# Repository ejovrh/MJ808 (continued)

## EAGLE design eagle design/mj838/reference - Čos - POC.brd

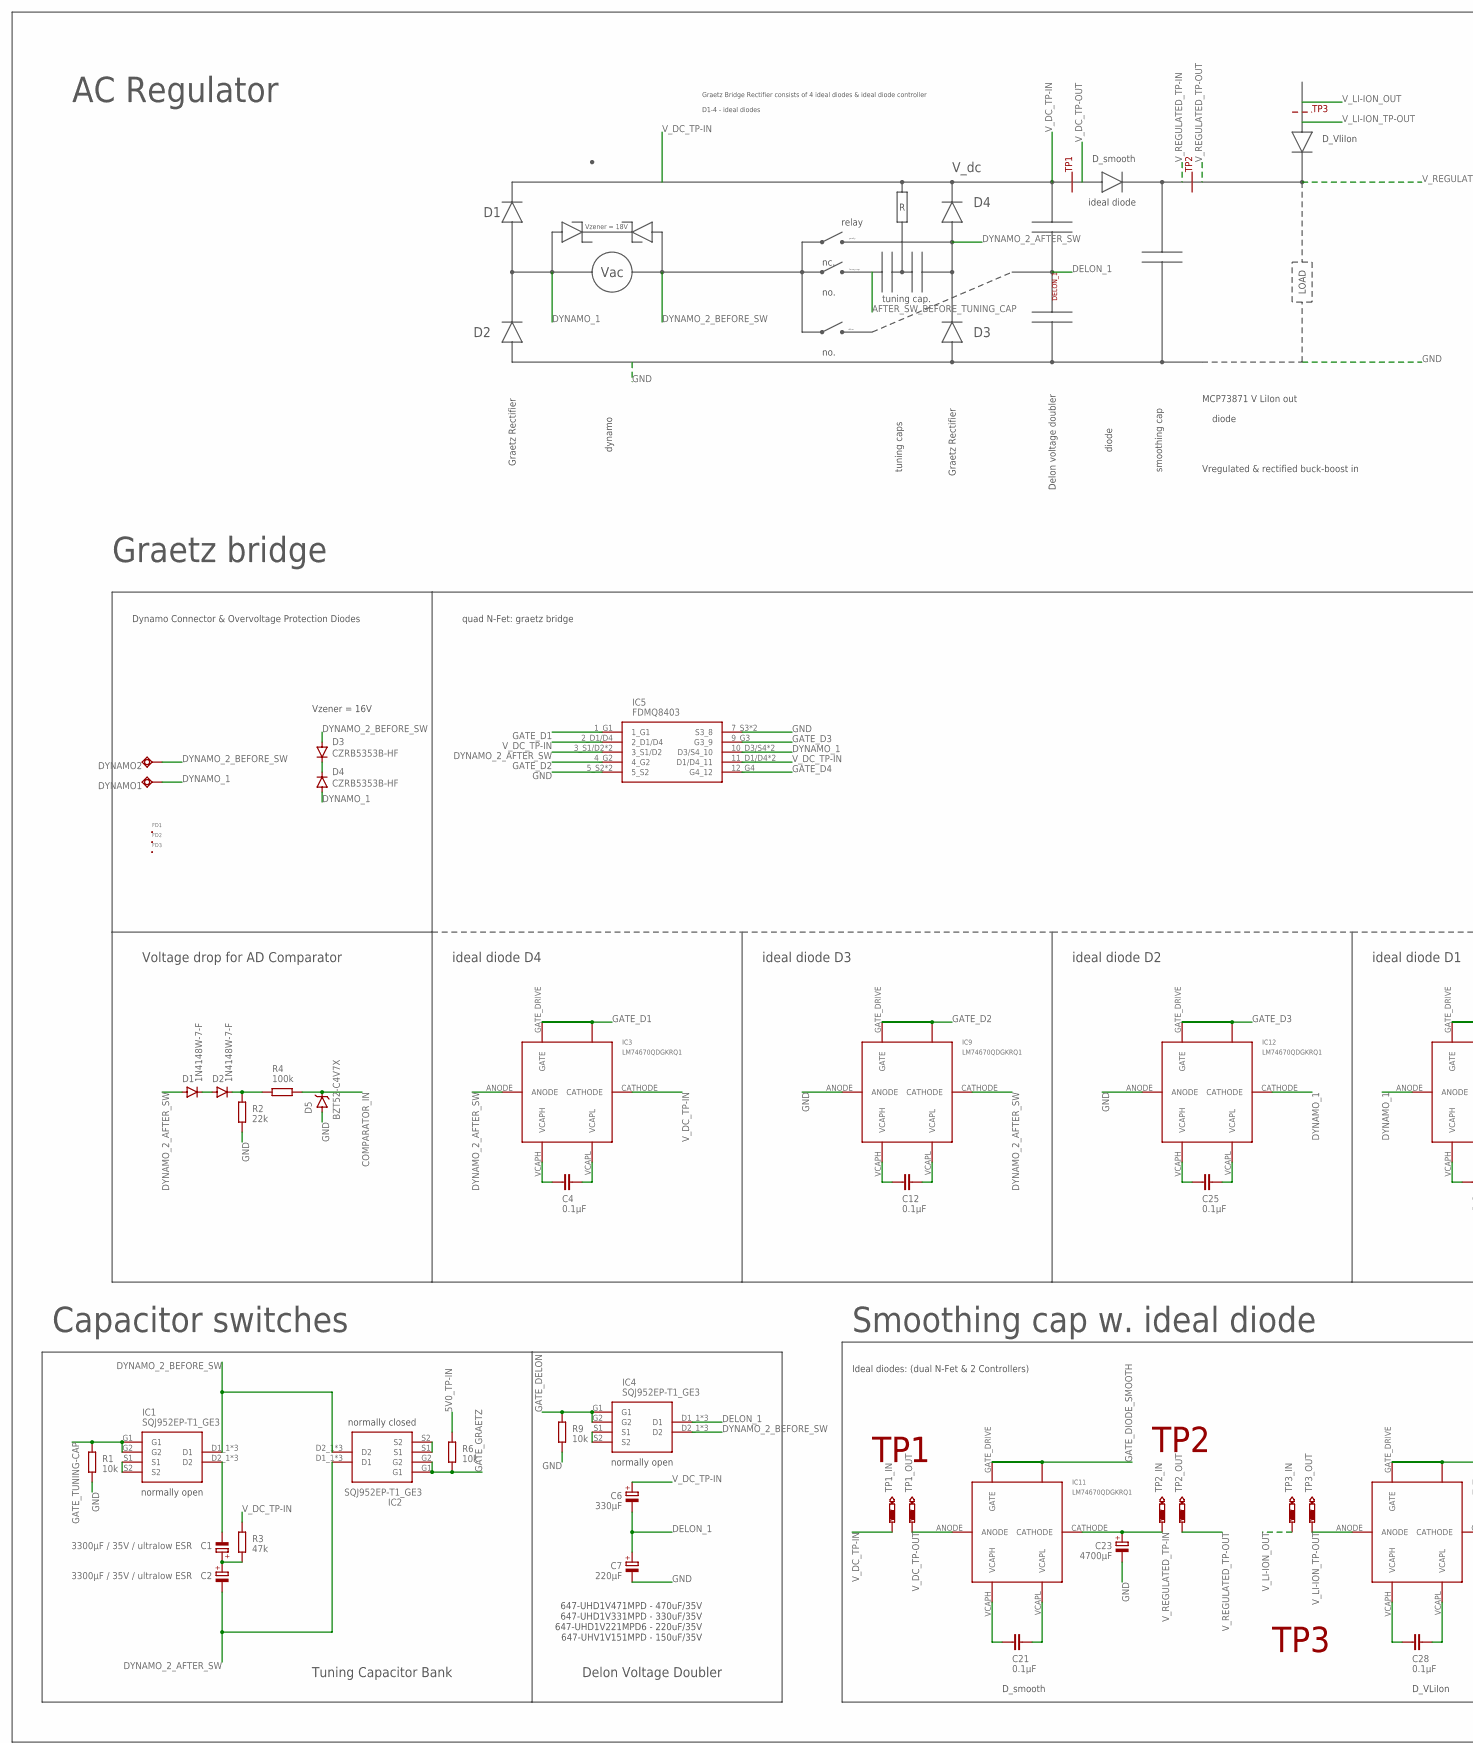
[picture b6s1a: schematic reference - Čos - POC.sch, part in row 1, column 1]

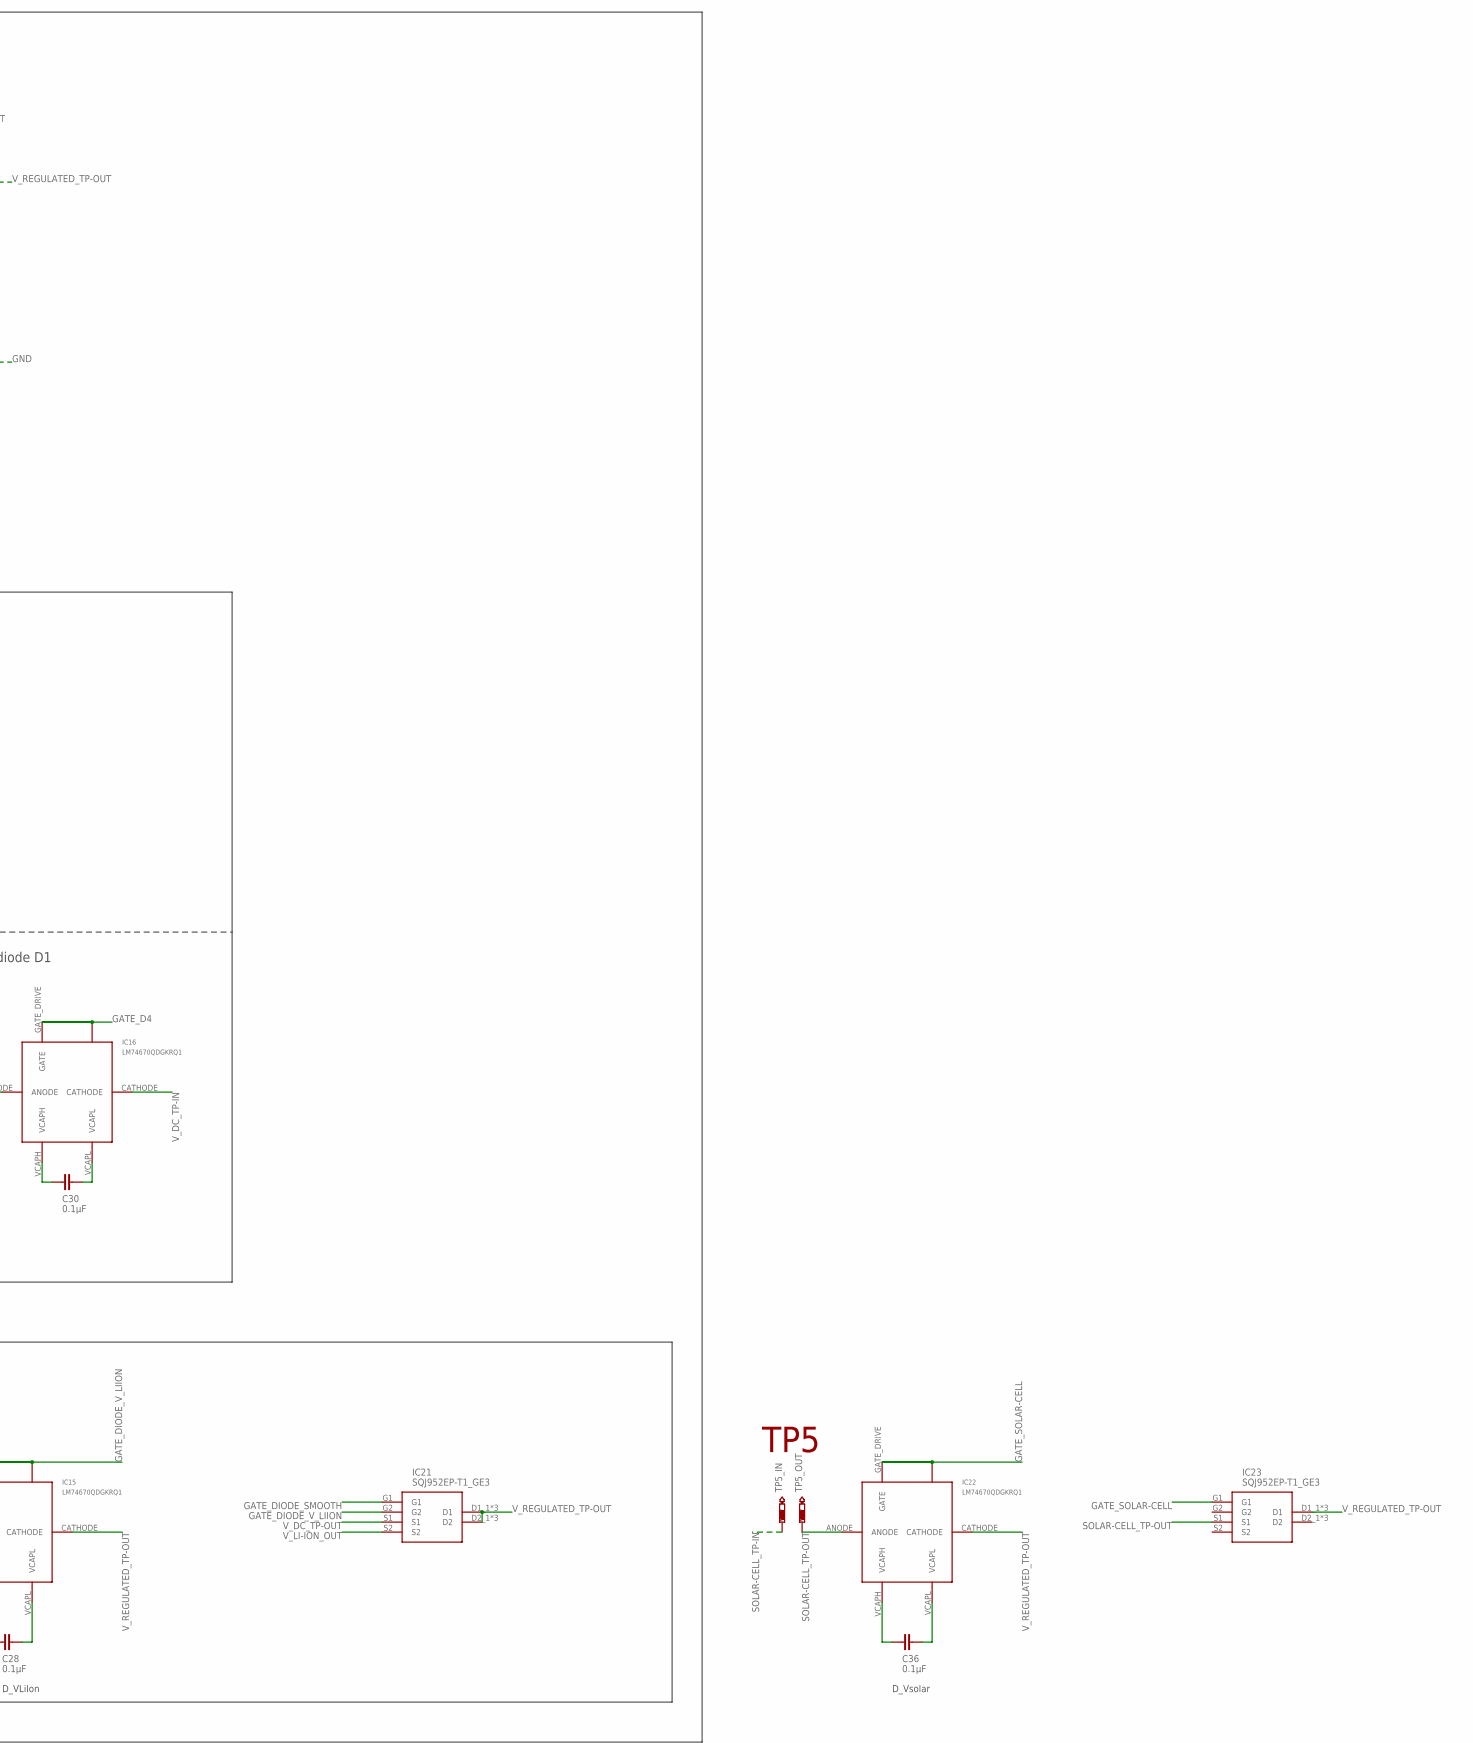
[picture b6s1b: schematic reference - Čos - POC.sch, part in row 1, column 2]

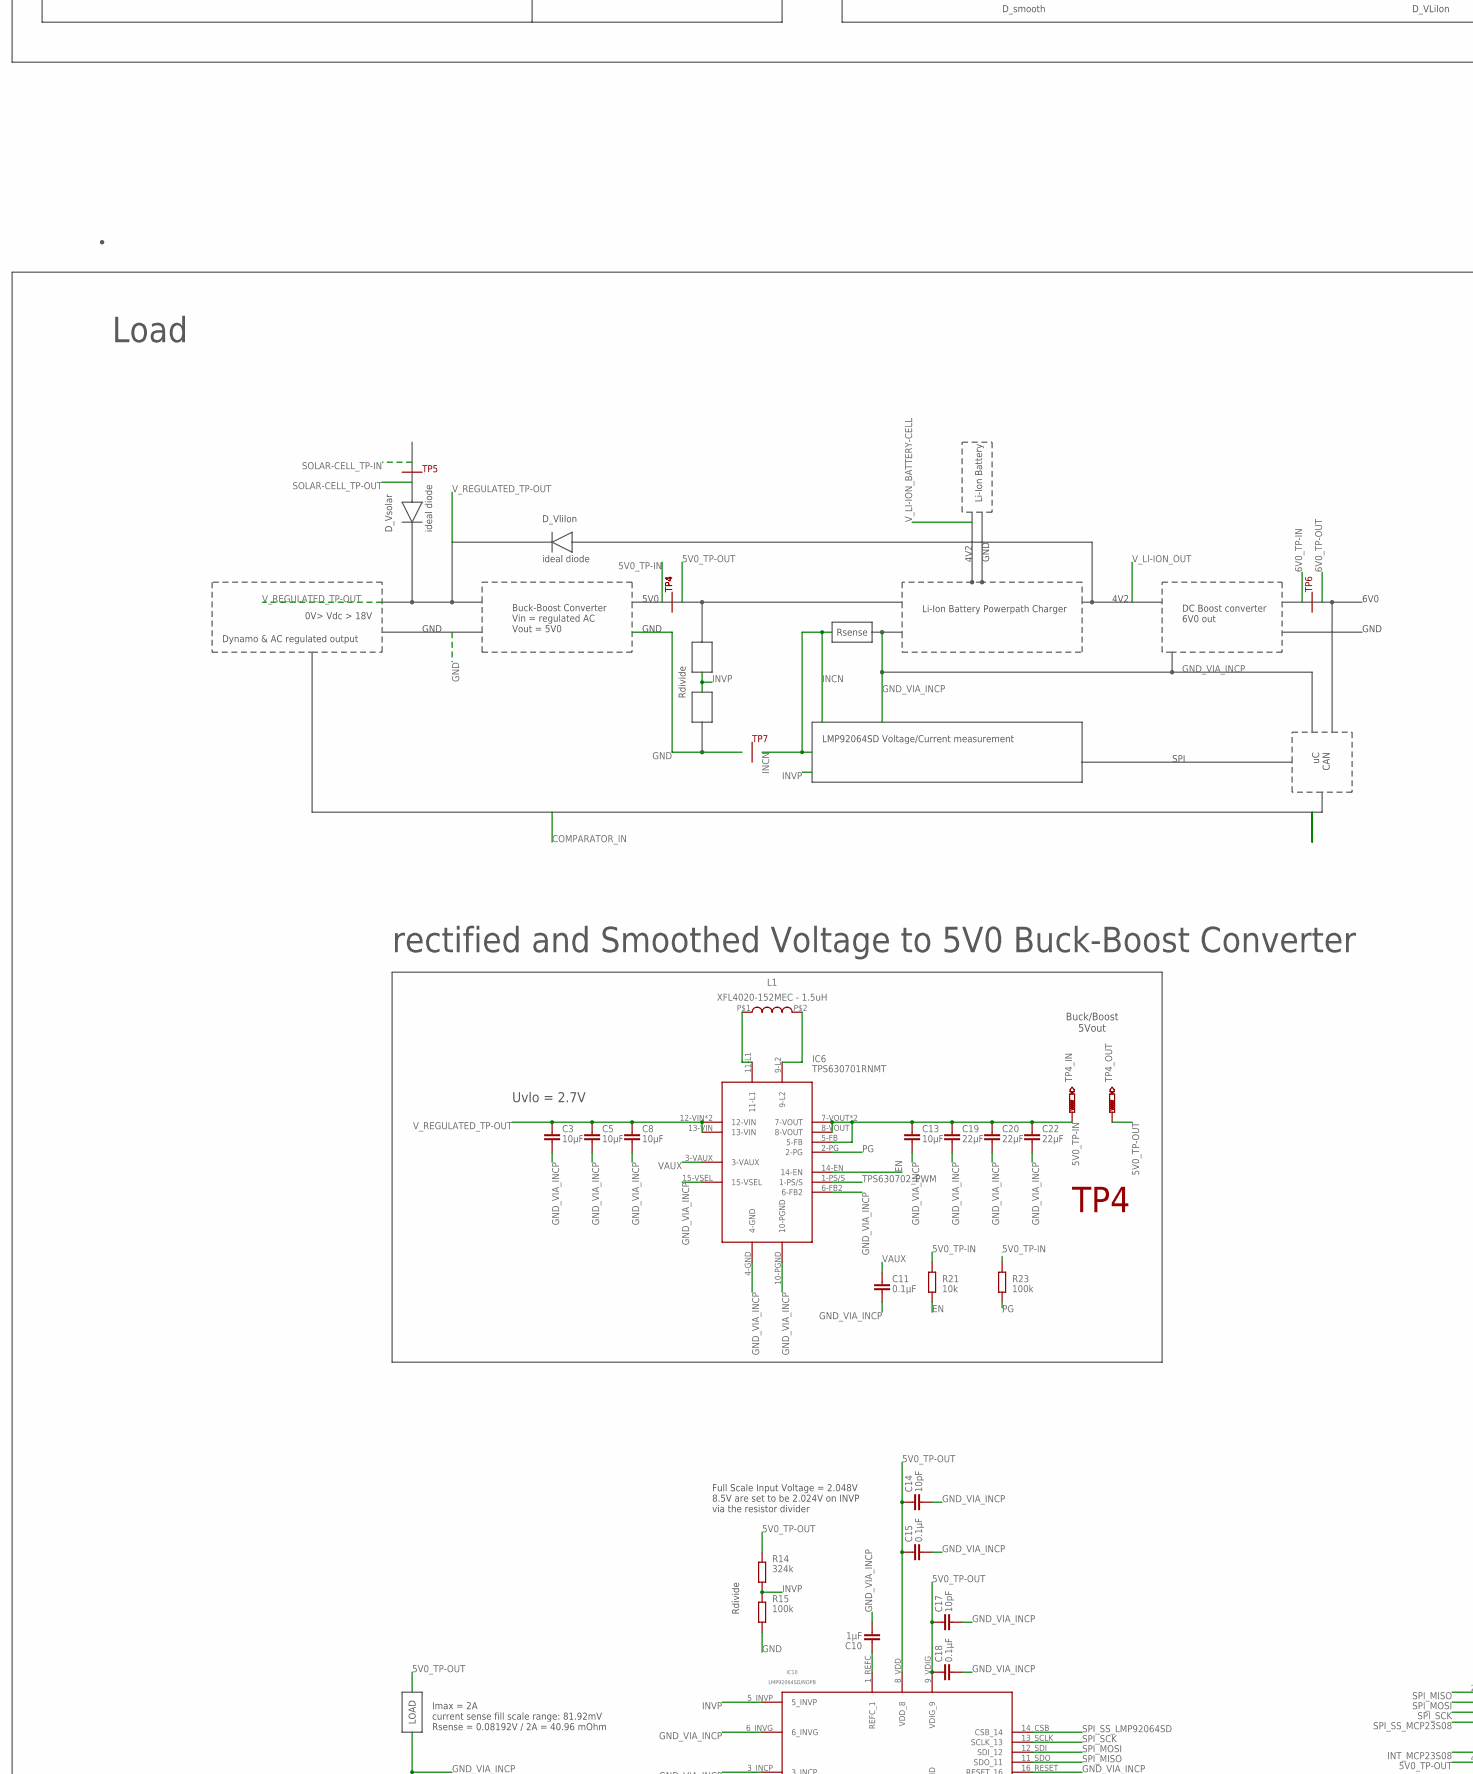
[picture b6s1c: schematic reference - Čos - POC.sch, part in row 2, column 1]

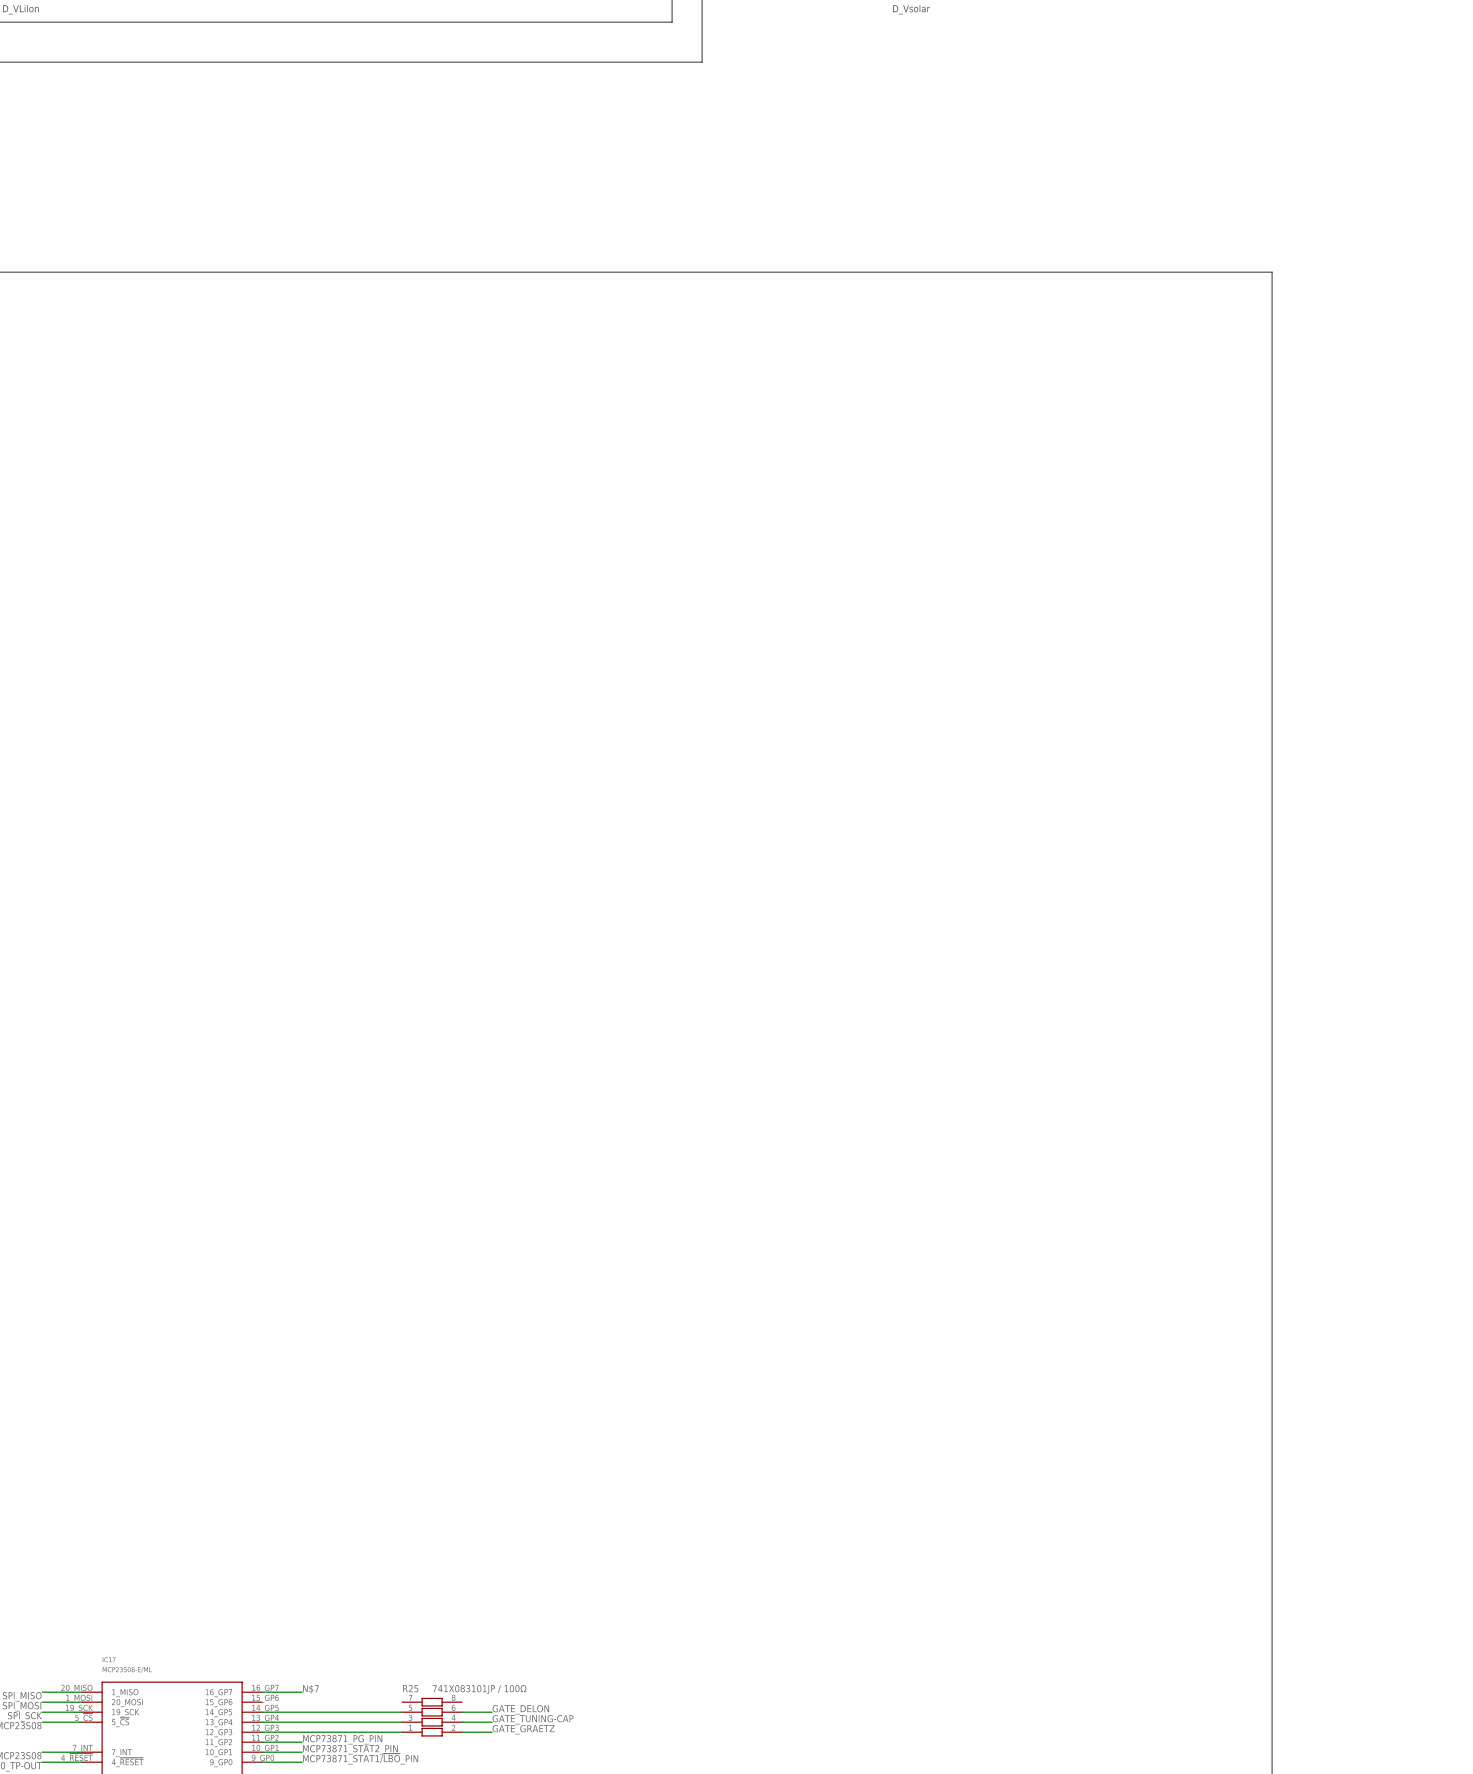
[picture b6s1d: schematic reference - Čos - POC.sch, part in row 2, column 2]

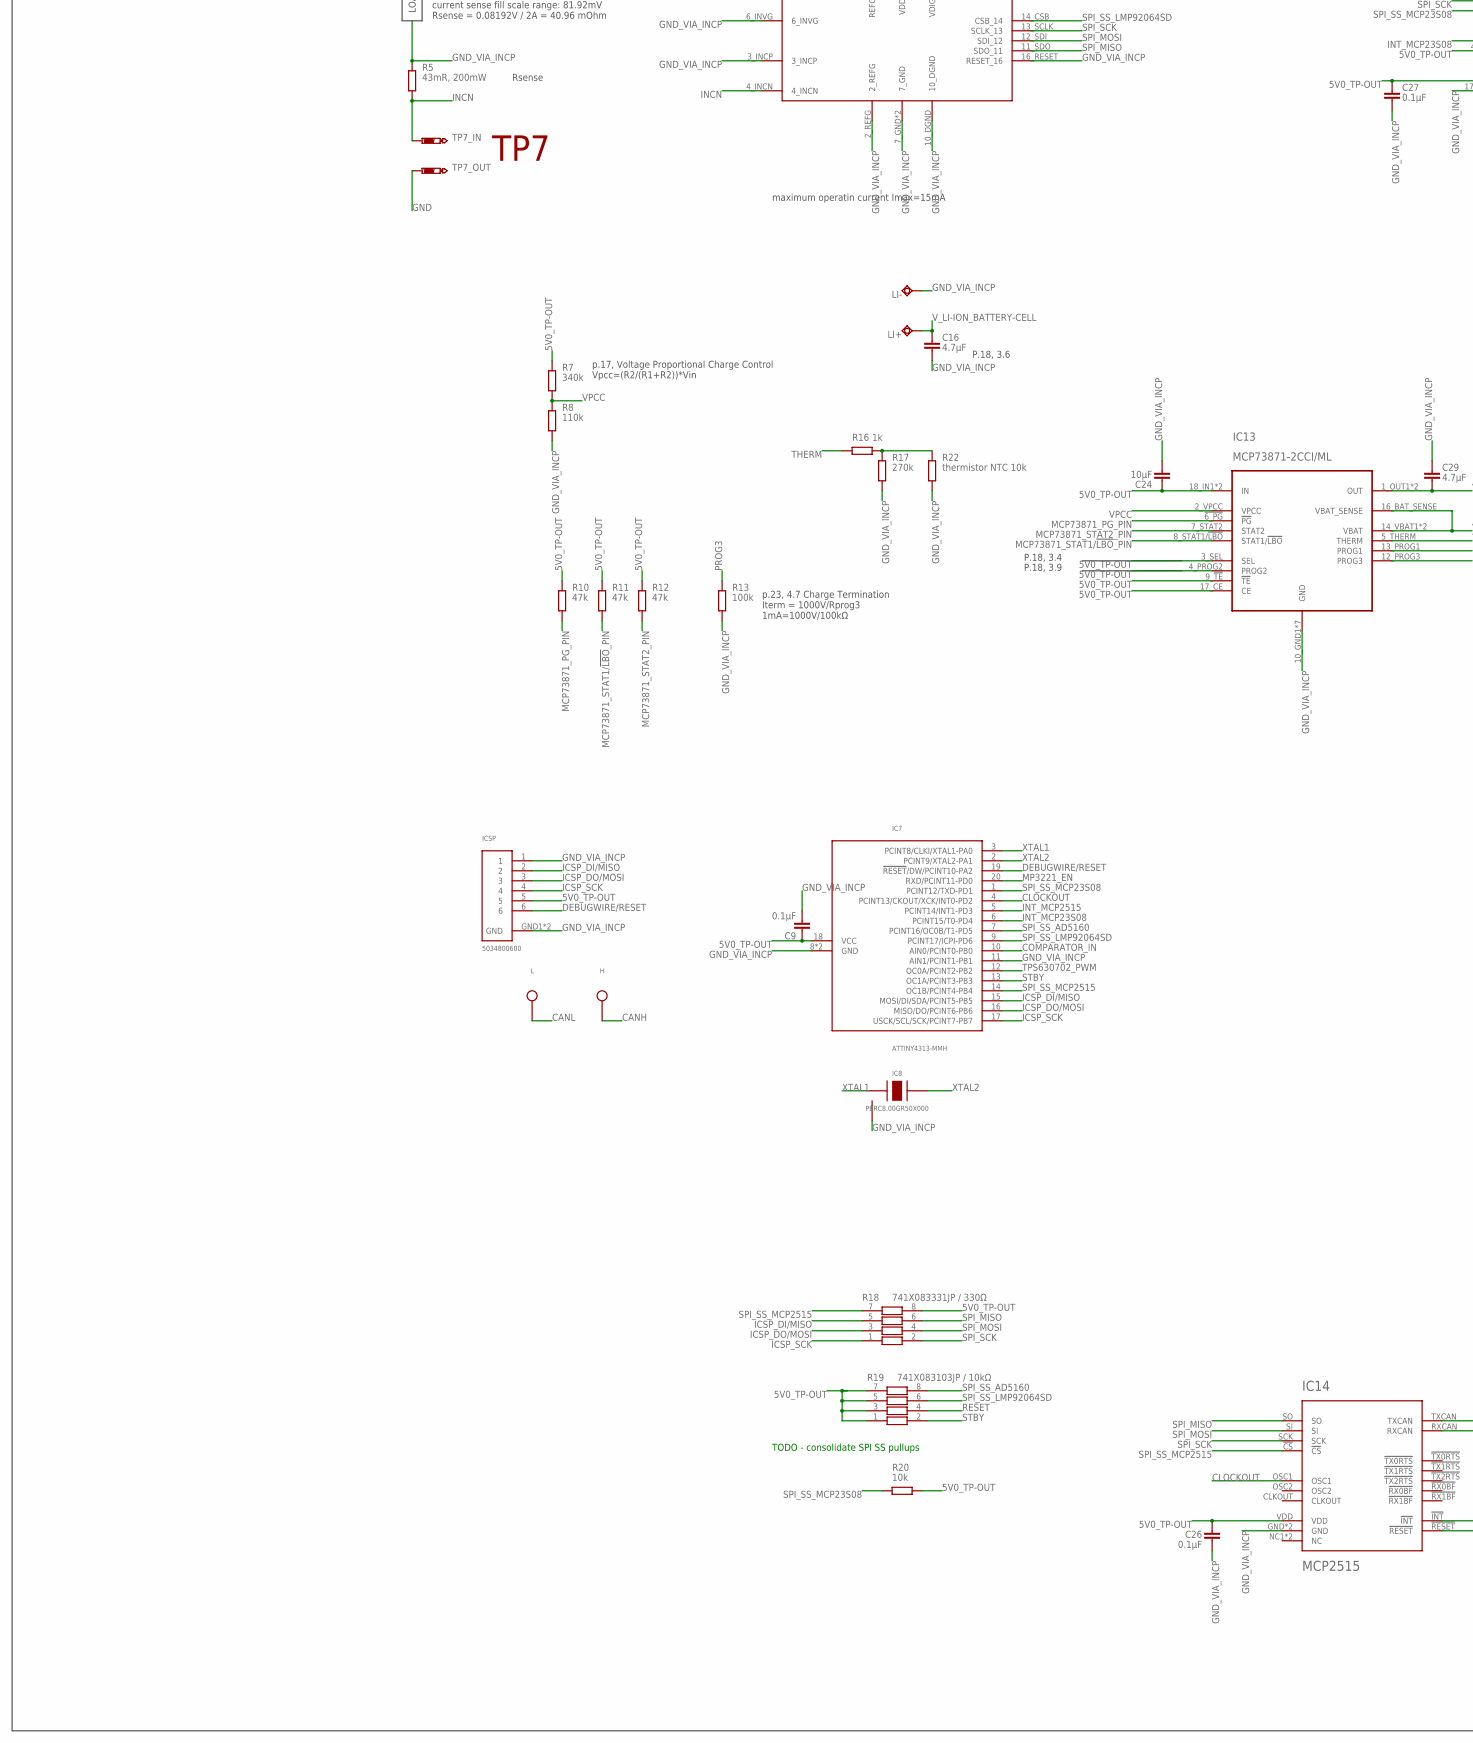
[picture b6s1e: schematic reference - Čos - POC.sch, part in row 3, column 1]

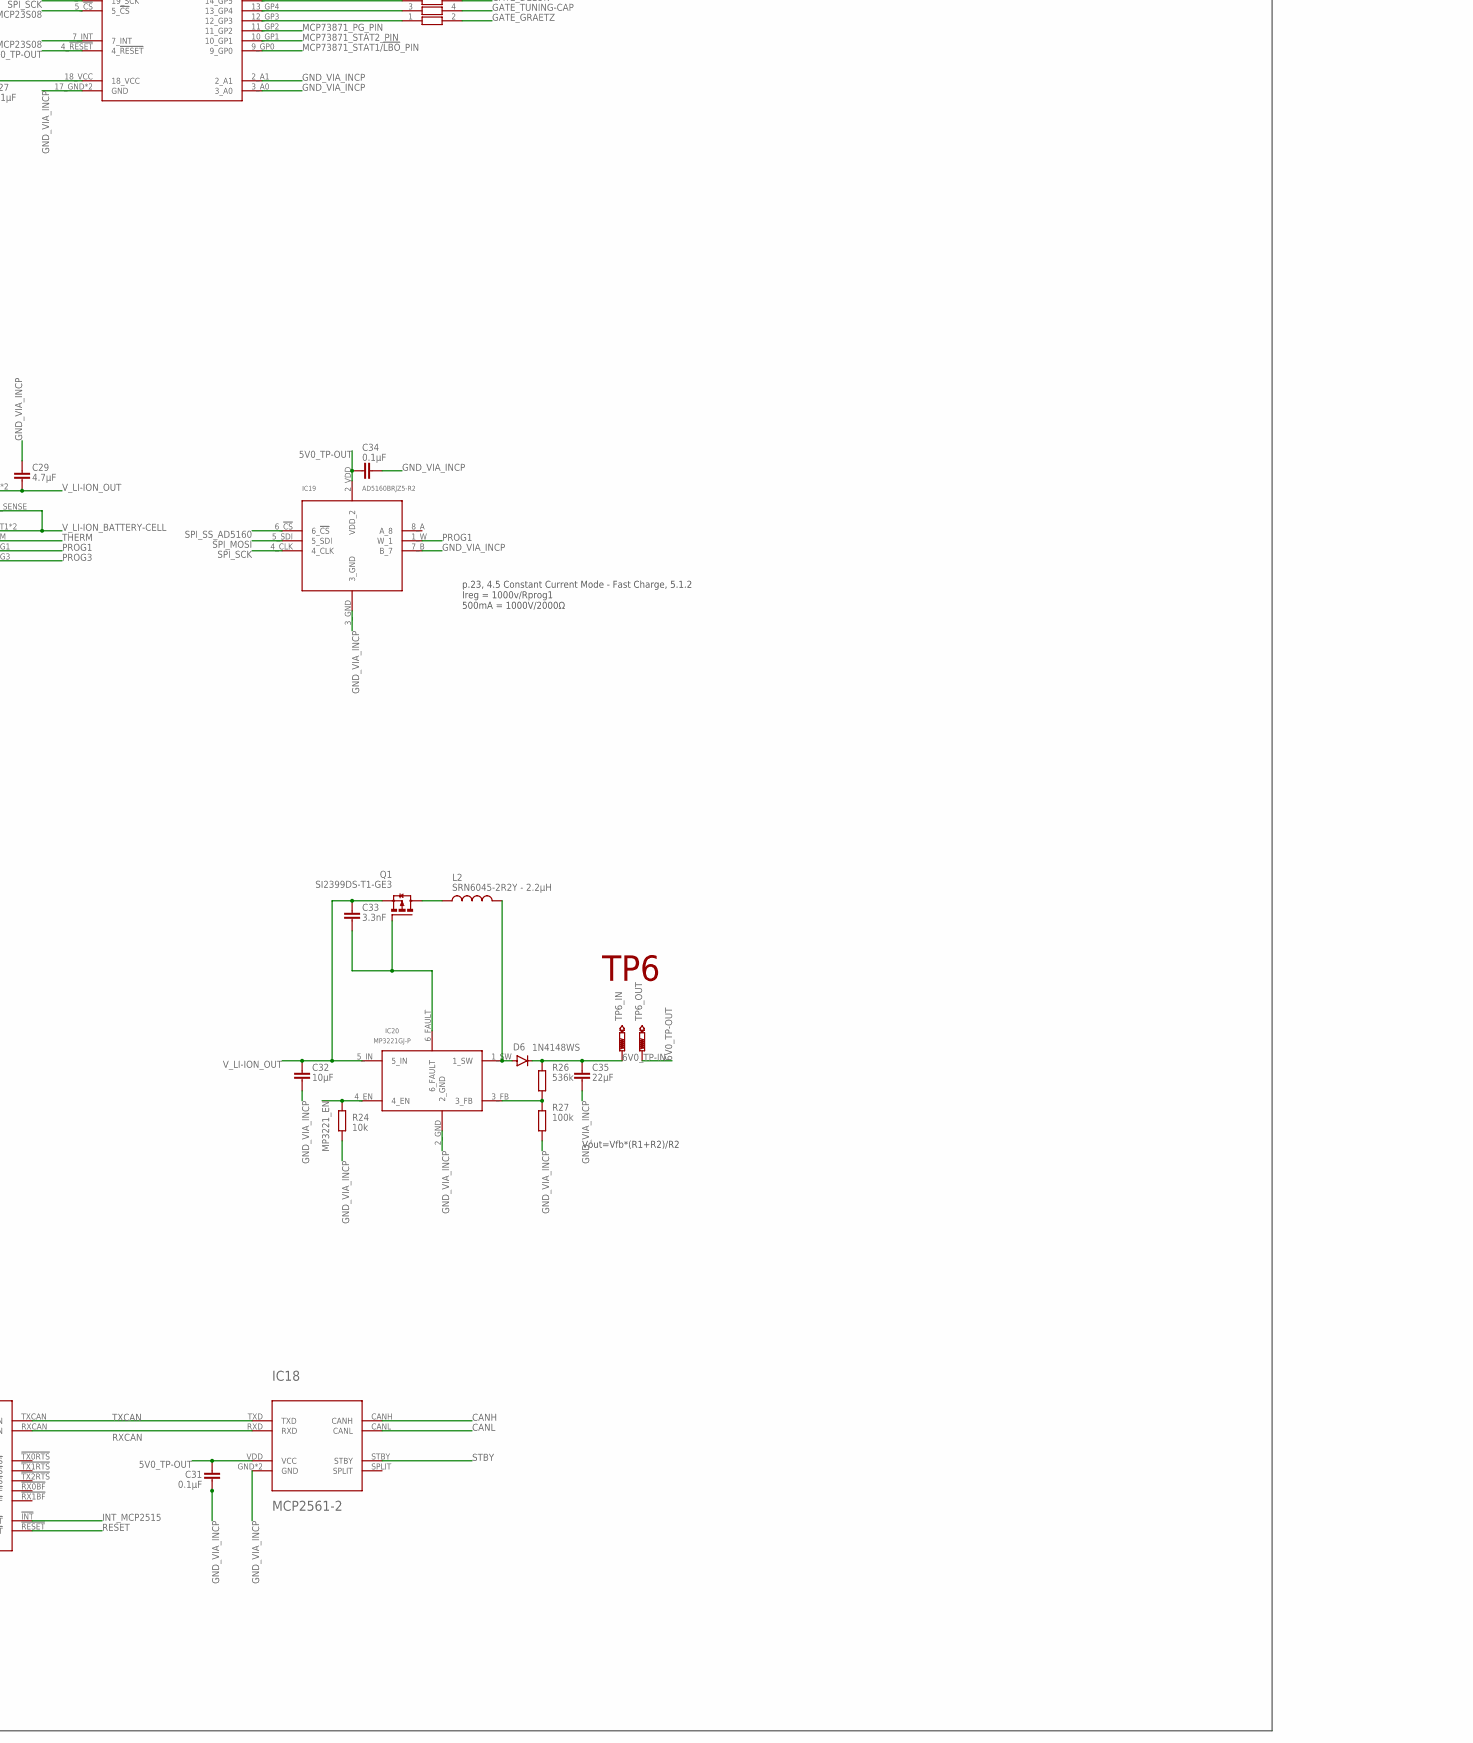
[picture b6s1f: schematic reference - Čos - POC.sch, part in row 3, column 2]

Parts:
C1, C2: 3300μF / 35V / ultralow ESR; E1,8-4
C3, C5: 10μF; C0805
C4, C9, C11, C12, C15, C18, C21, C25, C26, C27, C28, C30, C31, C34, C36: 0.1μF; C0402
C6: 330μF; E1,8-4
C7: 220μF; E1,8-4
C8, C13: 10μF; C0603
C10: 1μF; C0402
C14, C17: 10pF; C0402
C16, C29: 4.7μF; C0402
C19, C20, C22, C35: 22μF; C0805
C23: 4700μF; E1,8-4
C24, C32: 10μF; C0402
C33: 3.3nF; C0402
D1, D2: 1N4148W-7-F; SOD-123_MINI-SMA
D3, D4: CZRB5353B-HF; DO214AA
D5: BZT52-C4V7X; SOD-123
D6: 1N4148WS; SOD-323
DYNAMO1, DYNAMO2: Li-Ion Cell +; P1-13
FD1, FD2, FD3: FID_40MIL; FID_040
H: CAN High; SMT-1.2MM
IC1, IC2, IC4, IC21, IC23: SQJ952EP-T1_GE3; SO-8L
IC3, IC9, IC11, IC12, IC15, IC16, IC22: LM74670QDGKRQ1; VSSOP-8
IC5: FDMQ8403; MLP-12
IC6: TPS630701RNMT; VQFN
IC7: ATTINY4313-MMH; VQFN-20
IC8: PBRC8.00GR50X000; SMT
IC10: LMP92064SD/NOPB; WSON-16
IC13: MCP73871-2CCI/ML; QFN50P400X400X100-21N
IC14: MCP2515; QFN20
IC17: MCP23S08-E/ML; QFN20
IC18: MCP2561-2; DFN10
IC19: AD5160BRJZ5-R2; SOT-23-8
IC20: MP3221GJ-P; TSOT23-6
ICSP: 5034800600; SMT
L: CAN Low; SMT-1.2MM
L1: XFL4020-152MEC - 1.5uH; SMD
L2: SRN6045-2R2Y - 2.2μH; DJNR6045-100-S
LI+: Li-Ion Cell +; P1-13
LI-: Li-Ion Cell +; P1-13
Q1: SI2399DS-T1-GE3; SOT23
R1, R6, R9, R20, R21, R24: 10k; R0402
R2: 22k; R0402
R3, R10, R11, R12: 47k; R0402
R4, R13, R15, R23, R27: 100k; R0402
R5: 43mR, 200mW; R2512
R7: 340k; R0402
R8: 110k; R0402
R14: 324k; R0402
R16: 1k; R0402
R17: 270k; R0402
R18: 741X083331JP / 330Ω; 0402
R19: 741X083103JP / 10kΩ; 0402
R22: thermistor NTC 10k; V526-0
R25: 741X083101JP / 100Ω; 0402
R26: 536k; R0402
TP1_IN, TP1_OUT, TP2_IN, TP2_OUT, TP3_IN, TP3_OUT, TP4_IN, TP4_OUT, TP5_IN, TP5_OUT, TP6_IN, TP6_OUT, TP7_IN, TP7_OUT: PTR1TP10SQ; TP10SQ

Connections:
5V0_TP-IN: C13.1, C19.1, C20.1, C22.1, IC6.5-FB, IC6.7-VOUT, IC6.8-VOUT, IC6.VOUT (7-VOUT), R6.2, R21.2, R23.2, TP4_IN.TP
5V0_TP-OUT: C9.1, C14.1, C15.1, C17.1, C18.1, C24.1, C26.1, C27.1, C31.1, C34.1, IC7.18 (VCC), IC10.8_VDD (VDD_8), IC10.9_VDIG (VDIG_9), IC13.3_SEL (SEL), IC13.4_PROG2 (PROG2), IC13.9_!TE! (!TE!), IC13.17_CE (CE), IC13.18_IN1 (IN), IC13.19_IN2 (IN), IC14.VDD, IC17.4_!RESET!, IC17.18_VCC, IC18.VDD (VCC), IC19.2_VDD (VDD_2), ICSP.5, R7.2, R10.2, R11.2, R12.2, R14.2, R18.8, R19.1, R19.3, R19.5, R19.7, R20.2, TP4_OUT.TP
6V0_TP-IN: C35.1, D6.C, R26.2, TP6_IN.TP
6V0_TP-OUT: TP6_OUT.TP
AFTER_SW_BEFORE_TUNING_CAP: C1.-, IC1.D2_1 (D2), IC1.D2_2 (D2), IC1.D2_3 (D2)
CANH: H.P$1, IC18.CANH
CANL: IC18.CANL, L.P$1
CLOCKOUT: IC7.4 (PCINT13/CKOUT/XCK/INT0-PD2), IC14.OSC1
COMPARATOR_IN: D5.C, IC7.10 (AIN0/PCINT0-PB0), R4.2
D1_VCAPH: C4.2, IC3.VCAPH
D1_VCAPL: C4.1, IC3.VCAPL
D2_VCAPH: C12.2, IC9.VCAPH
D2_VCAPL: C12.1, IC9.VCAPL
D3_VCAPH: C25.2, IC12.VCAPH
D3_VCAPL: C25.1, IC12.VCAPL
D4_VCAPH: C30.2, IC16.VCAPH
D4_VCAPL: C30.1, IC16.VCAPL
DEBUGWIRE/RESET: IC7.19 (!RESET!/DW/PCINT10-PA2), ICSP.6
DELON_1: C6.-, C7.+, IC4.D1_1 (D1), IC4.D1_2 (D1), IC4.D1_3 (D1)
DYNAMO_1: D4.A, DYNAMO1.TP, IC5.10_D3/S4 (D3/S4_10), IC5.D3/S4 (D3/S4_10), IC12.CATHODE, IC16.ANODE
DYNAMO_2_AFTER_SW: C2.-, D1.A, IC2.D1_1 (D1), IC2.D1_2 (D1), IC2.D1_3 (D1), IC3.ANODE, IC5.3_S1/D2, IC5.S1/D2 (3_S1/D2), IC9.CATHODE
DYNAMO_2_BEFORE_SW: D3.A, DYNAMO2.TP, IC1.D1_1 (D1), IC1.D1_2 (D1), IC1.D1_3 (D1), IC2.D2_1 (D2), IC2.D2_2 (D2), IC2.D2_3 (D2), IC4.D2_1 (D2), IC4.D2_2 (D2), IC4.D2_3 (D2)
D_SMOOTH_VCAP: C21.1, IC11.VCAPL
D_SMOOTH_VCAPH: C21.2, IC11.VCAPH
D_VLIION_VCAPH: C28.2, IC15.VCAPH
D_VLIION_VCAPH1: C36.2, IC22.VCAPH
D_VLIION_VCAPL: C28.1, IC15.VCAPL
D_VLIION_VCAPL1: C36.1, IC22.VCAPL
EN: IC6.14-EN, R21.1
FB: IC20.3_FB, R26.1, R27.2
GATE_D1: IC3.GATE_DRIVE (GATE), IC3.GATE_PULLD, IC5.1_G1
GATE_D2: IC5.4_G2, IC9.GATE_DRIVE (GATE), IC9.GATE_PULLD
GATE_D3: IC5.9_G3 (G3_9), IC12.GATE_DRIVE (GATE), IC12.GATE_PULLD
GATE_D4: IC5.12_G4 (G4_12), IC16.GATE_DRIVE (GATE), IC16.GATE_PULLD
GATE_DELON: IC4.G1, IC4.G2, R9.2, R25.6
GATE_DIODE_SMOOTH: IC11.GATE_DRIVE (GATE), IC11.GATE_PULLD, IC21.G1
GATE_DIODE_V_LIION: IC15.GATE_DRIVE (GATE), IC15.GATE_PULLD, IC21.G2
GATE_GRAETZ: IC2.G1, IC2.G2, R6.1, R25.2
GATE_SOLAR-CELL: IC22.GATE_DRIVE (GATE), IC22.GATE_PULLD, IC23.G1
GATE_TUNING-CAP: IC1.G1, IC1.G2, R1.2, R25.4
GND: C7.-, C23.-, D5.A, IC5.5_S2, IC5.6_S2 (5_S2), IC5.7_S3 (S3_8), IC5.8_S3 (S3_8), IC9.ANODE, IC12.ANODE, R1.1, R2.1, R9.1, R15.1, TP7_OUT.TP
GND_VIA_INCP: C3.2, C5.2, C8.2, C9.2, C10.2, C11.2, C13.2, C14.2, C15.2, C16.2, C17.2, C18.2, C19.2, C20.2, C22.2, C24.2, C26.2, C27.2, C29.1, C31.2, C32.2, C34.2, C35.2, IC6.4-GND, IC6.6-FB2, IC6.10-PGND, IC6.15-VSEL, IC7.8 (GND), IC7.11 (AIN1/PCINT1-PB1), IC7.GND, IC8.GND, IC10.2_REFG, IC10.3_INCP, IC10.6_INVG, IC10.7_GND, IC10.10_DGND, IC10.16_RESET (RESET_16), IC10.GND1 (7_GND), IC13.10_GND1 (GND), IC13.11_GND2 (GND), IC13.GND2 (GND), IC13.GND3 (GND), IC13.GND4 (GND), IC13.GND5 (GND), IC13.GND6 (GND), IC14.GND, IC14.GND6 (GND), IC17.2_A1, IC17.3_A0, IC17.17_GND (GND), IC17.GND, IC18.GND, IC18.VSS (GND), IC19.3_GND, IC19.7_B (B_7), IC20.2_GND, ICSP.1, ICSP.GND1 (GND), ICSP.GND2 (GND), LI-.TP, R5.2, R8.1, R13.1, R17.1, R22.1, R24.2, R27.1
ICSP_DI/MISO: IC7.15 (MOSI/DI/SDA/PCINT5-PB5), ICSP.2, R18.5
ICSP_DO/MOSI: IC7.16 (MISO/DO/PCINT6-PB6), ICSP.3, R18.3
ICSP_SCK: IC7.17 (USCK/SCL/SCK/PCINT7-PB7), ICSP.4, R18.1
INCN: IC10.4_INCN, R5.1, TP7_IN.TP
INT_MCP23S08: IC7.6 (PCINT15/T0-PD4), IC17.7_INT
INT_MCP2515: IC7.5 (PCINT14/INT1-PD3), IC14.!INT!
INVP: IC10.5_INVP, R14.1, R15.2
MCP73871_PG_PIN: IC13.!6_PG! (!PG!), IC17.11_GP2, R10.1
MCP73871_STAT1/!LBO!_PIN: IC13.8_STAT1/!LBO! (STAT1/!LBO!), IC17.9_GP0, R11.1
MCP73871_STAT2_PIN: IC13.7_STAT2 (STAT2), IC17.10_GP1, R12.1
MP3221_EN: IC7.20 (RXD/PCINT11-PD0), IC20.4_EN, R24.1
MP3221_FAULT: C33.2, IC20.6_FAULT, Q1.1 (G)
unnamed: IC6.11-L1, L1.P$1
unnamed: L2.1, Q1.3 (D)
unnamed: D1.C, D2.A
unnamed: D2.C, R2.2, R4.1
unnamed: IC6.9-L2, L1.P$2
unnamed: IC17.14_GP5, R25.5
unnamed: R16.2, R17.2, R22.2
unnamed: IC17.13_GP4, R25.3
unnamed: IC17.12_GP3, R25.1
unnamed: IC1.S1, IC1.S2
unnamed: IC2.S1, IC2.S2
unnamed: C10.1, IC10.1_REFC (REFC_1)
unnamed: IC4.S1, IC4.S2
PG: IC6.2-PG, R23.1
PROG1: IC13.13_PROG1 (PROG1), IC19.1_W (W_1)
PROG3: IC13.12_PROG3 (PROG3), R13.2
RESET: IC14.!RESET!, R19.4
RXCAN: IC14.RXCAN, IC18.RXD
SOLAR-CELL_TP-IN: TP5_IN.TP
SOLAR-CELL_TP-OUT: IC22.ANODE, IC23.S1, TP5_OUT.TP
SPI_MISO: IC10.11_SDO (SDO_11), IC14.SO, IC17.20_MISO (1_MISO), R18.6
SPI_MOSI: IC10.12_SDI (SDI_12), IC14.SI, IC17.1_MOSI (20_MOSI), IC19.5_SDI, R18.4
SPI_SCK: IC10.13_SCLK (SCLK_13), IC14.SCK, IC17.19_SCK, IC19.4_CLK, R18.2
SPI_SS_AD5160: IC7.7 (PCINT16/OC0B/T1-PD5), IC19.6_!CS!, R19.8
SPI_SS_LMP92064SD: IC7.9 (PCINT17/ICPI-PD6), IC10.14_CSB (CSB_14), R19.6
SPI_SS_MCP23S08: IC7.1 (PCINT12/TXD-PD1), IC17.5_!CS!, R20.1
SPI_SS_MCP2515: IC7.14 (OC1B/PCINT4-PB4), IC14.!CS!, R18.7
STBY: IC7.13 (OC1A/PCINT3-PB3), IC18.STBY, R19.2
SW: D6.A, IC20.1_SW, L2.2
THERM: IC13.5_THERM (THERM), R16.1
TPS630702_PWM: IC6.1-PS/S, IC7.12 (OC0A/PCINT2-PB2)
TUNIN_CAP2_BIAS: C1.+, C2.+, R3.1
TXCAN: IC14.TXCAN, IC18.TXD
VAUX: C11.1, IC6.3-VAUX
VPCC: IC13.2_VPCC (VPCC), R7.1, R8.2
V_DC_TP-IN: C6.+, IC3.CATHODE, IC5.2_D1/D4, IC5.11_D1/D4 (D1/D4_11), IC5.D1/D4 (D1/D4_11), IC16.CATHODE, R3.2, TP1_IN.TP
V_DC_TP-OUT: IC11.ANODE, IC21.S1, TP1_OUT.TP
V_LI-ION_BATTERY-CELL: C16.1, IC13.14_VBAT1 (VBAT), IC13.15_VBAT2 (VBAT), IC13.16_BAT_SENSE (VBAT_SENSE), LI+.TP
V_LI-ION_OUT: C29.2, C32.1, C33.1, IC13.1_OUT1 (OUT), IC13.20_OUT2 (OUT), IC20.5_IN, IC21.S2, Q1.2 (S), TP3_IN.TP
V_LI-ION_TP-OUT: IC15.ANODE, TP3_OUT.TP
V_REGULATED_TP-IN: C23.+, IC11.CATHODE, TP2_IN.TP
V_REGULATED_TP-OUT: C3.1, C5.1, C8.1, IC6.12-VIN, IC6.13-VIN, IC6.VIN (12-VIN), IC15.CATHODE, IC21.D1_1 (D1), IC21.D1_2 (D1), IC21.D1_3 (D1), IC21.D2_1 (D2), IC21.D2_2 (D2), IC21.D2_3 (D2), IC22.CATHODE, IC23.D1_1 (D1), IC23.D1_2 (D1), IC23.D1_3 (D1), TP2_OUT.TP
XTAL1: IC7.3 (PCINT8/CLKI/XTAL1-PA0), IC8.XTAL1
XTAL2: IC7.2 (PCINT9/XTAL2-PA1), IC8.XTAL2
ZENER_COMMON: D3.C, D4.C

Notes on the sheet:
P.18, 3.6
p.23, 4.5 Constant Current Mode - Fast Charge, 5.1.2 Ireg = 1000v/Rprog1 500mA = 1000V/2000Ω
p.23, 4.7 Charge Termination Iterm = 1000V/Rprog3 1mA=1000V/100kΩ
p.17, Voltage Proportional Charge Control Vpcc=(R2/(R1+R2))*Vin
P.18, 3.4
P.18, 3.9
Vout=Vfb*(R1+R2)/R2
Vzener = 16V
ideal diode D1
ideal diode D2
ideal diode D3
ideal diode D4
Tuning Capacitor Bank
Delon Voltage Doubler
quad N-Fet: graetz bridge
V_dc
Vac
Graetz Bridge Rectifier consists of 4 ideal diodes & ideal diode controller D1-4 - ideal diodes
tuning cap.
Dynamo Connector & Overvoltage Protection Diodes
smoothing cap
LOAD
Graetz Rectifier
Delon voltage doubler
relay
nc.
no.
normally open
normally closed
ideal diode
TP1
TP2
AC Regulator
Load
rectified and Smoothed Voltage to 5V0 Buck-Boost Converter
Buck-Boost Converter Vin = regulated AC Vout = 5V0
5V0
GND
Dynamo & AC regulated output
Li-Ion Battery Powerpath Charger

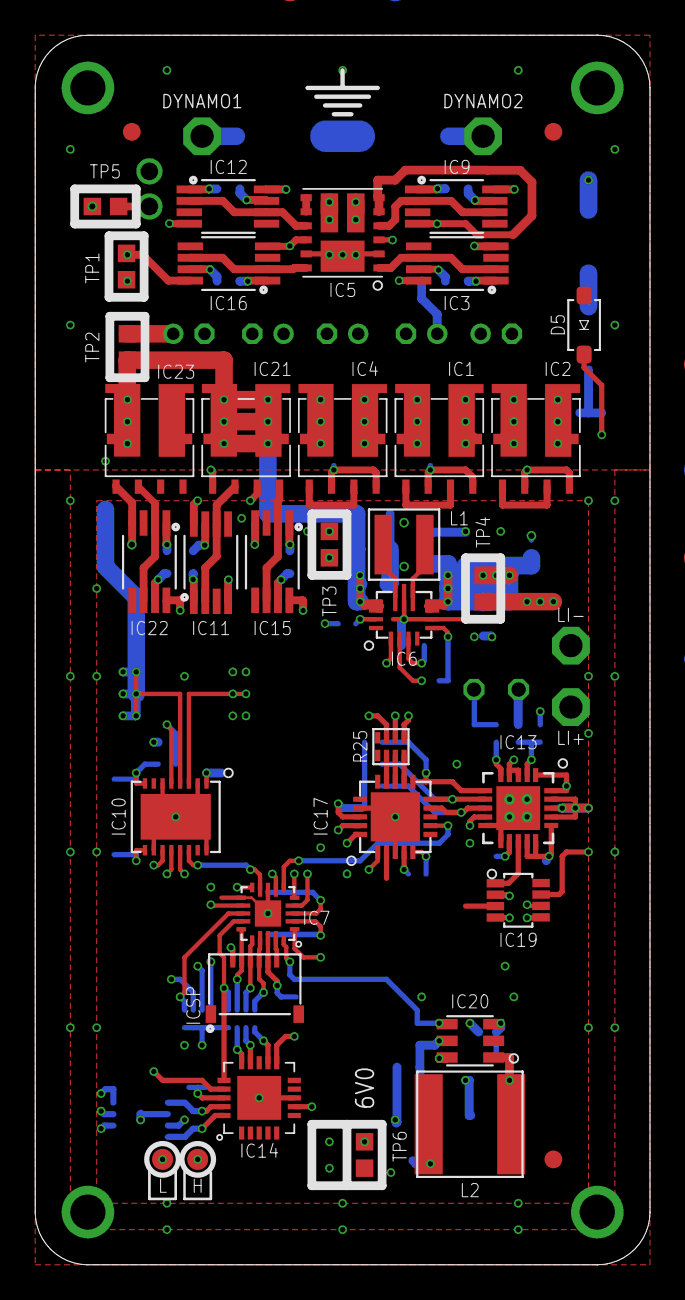
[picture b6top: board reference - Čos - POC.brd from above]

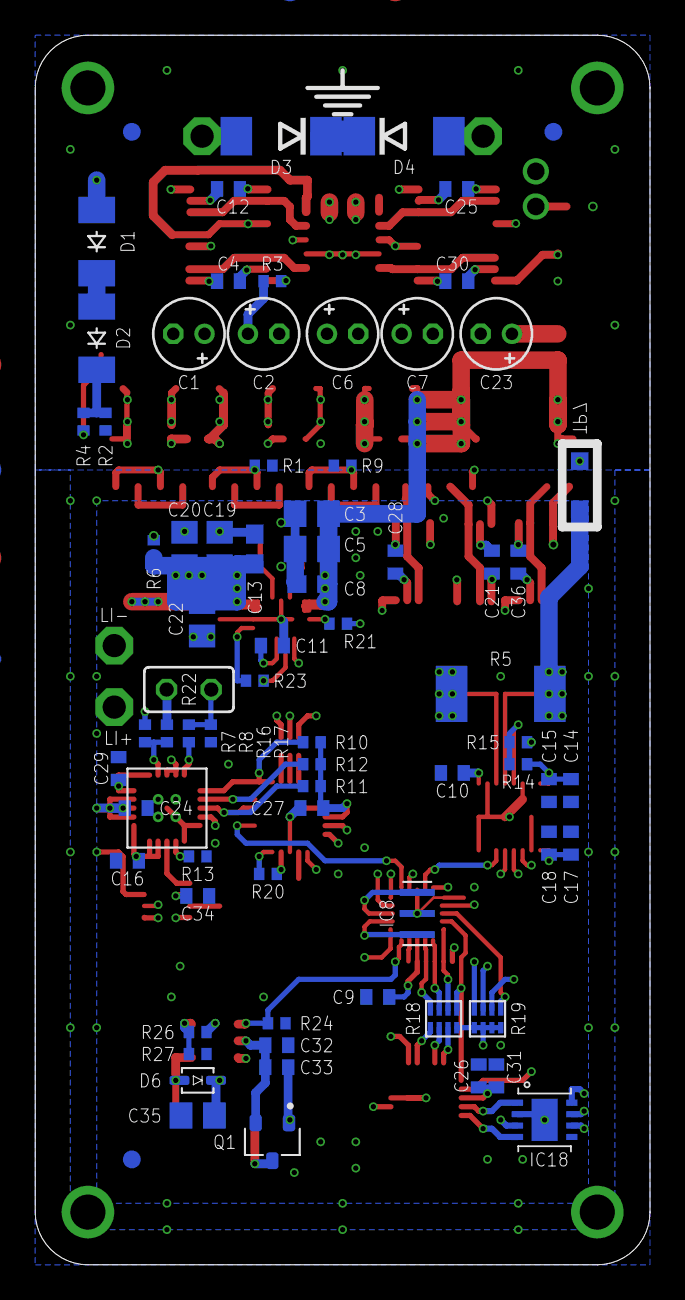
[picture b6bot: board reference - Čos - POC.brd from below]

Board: 4 copper layers, 35.0 x 70.0 mm, 119 parts (72 on the bottom side), 97 nets.
